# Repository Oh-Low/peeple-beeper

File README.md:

# PEEPLE BEEPER

A 128×64 FSTN LoRa pager. The C firmware under `firmware/` is shared by the desktop bench and the Feather nRF52840 image. The RP2350 board (v3, `hardware/rp2350`) has a schematic and no layout or firmware image yet. It replaces the ESP32-S3 board (v2).

Build, bench keys, and how to flash a Feather are below. The map of the tree is [docs/README.md](docs/README.md).

## Build

```
make test           # host tests, each prints ok
make bench          # build/peeple-emu (SDL2)
make run            # build it if needed, then open the window
make check-feather  # compile the Feather HAL table, no link and no flash
make bringup        # breadboard wire test, build/bringup.uf2
make flash-bringup  # copy that image onto FTHR840BOOT
make feather        # pager image, build/feather.uf2
make flash-feather  # copy that image onto FTHR840BOOT
```

`make feather` and `make bringup` need `arm-none-eabi-gcc`. Double-tap the Feather reset button so the `FTHR840BOOT` drive appears, then flash. The wire-test glass shows the switches, the compass ids, one radio register, and a count of GPS sentences. The pager image shows the menu.

`cmake -B build/cmake && cmake --build build/cmake` builds the same host tests and `peeple-emu`. It does not build a UF2.

## Bench

Install SDL2, then `make run`. On macOS, double-click `peeple-emu.command`.

```
brew install sdl2 pkg-config          # macOS
sudo apt install libsdl2-dev pkg-config   # Debian / Ubuntu
sudo dnf install SDL2-devel pkgconf-pkg-config   # Fedora
pacman -S mingw-w64-ucrt-x86_64-SDL2 mingw-w64-ucrt-x86_64-pkgconf   # MSYS2
```

Default bench is three radios at east 0 / 75 / 150 ft, all at north 0 (A reaches C only through B). **+ add** / **− remove** in the top bar grow the bench up to 16 units. Each column is a scaled 128×64 LCD, the radio name, its place on the foot grid, and who it can hear.

- Click an LCD to focus that radio
- Scroll or drag on the LCD = encoder
- Click = shaft press + release (Select)
- Esc = Back
- **N / W / E / S** move that radio on the foot grid. North is up. A step is 5 ft, Shift is 25 ft. Scrolling the panel under an LCD moves it north or south. Straight-line distance under 100 ft is radio range. `(1, 0)` is 1 ft east.
- **flat** / **tipped** and **still** / **moving** are the level check. Tipped is 25° off flat. **heading − / +** turns that radio. A step is 15°, Shift is 45°, and 0° means the top of the LCD points north.
- **sky** / **no sky** is whether a listen can see satellites. **sample** starts that listen now.
- j/k and arrows turn the knob; Enter/Space selects
- NVM is per user: `~/Library/Application Support/Peeple/Beeper/` on macOS, `~/.local/share/Peeple/Beeper/` on Linux, `%APPDATA%\Peeple\Beeper\` on Windows. A file still named `./emu-nvm-<id>.bin` in the current directory is read once, then saved in that folder.

The bench seeds contact books so A/B/C can Compose without walking HELLO. That directory is bench-only.

## Pair two pagers

1. Settings → Display name on each unit.
2. Add on both, hold the units together (RSSI ≥ −45).
3. Compose → peer name → canned line.

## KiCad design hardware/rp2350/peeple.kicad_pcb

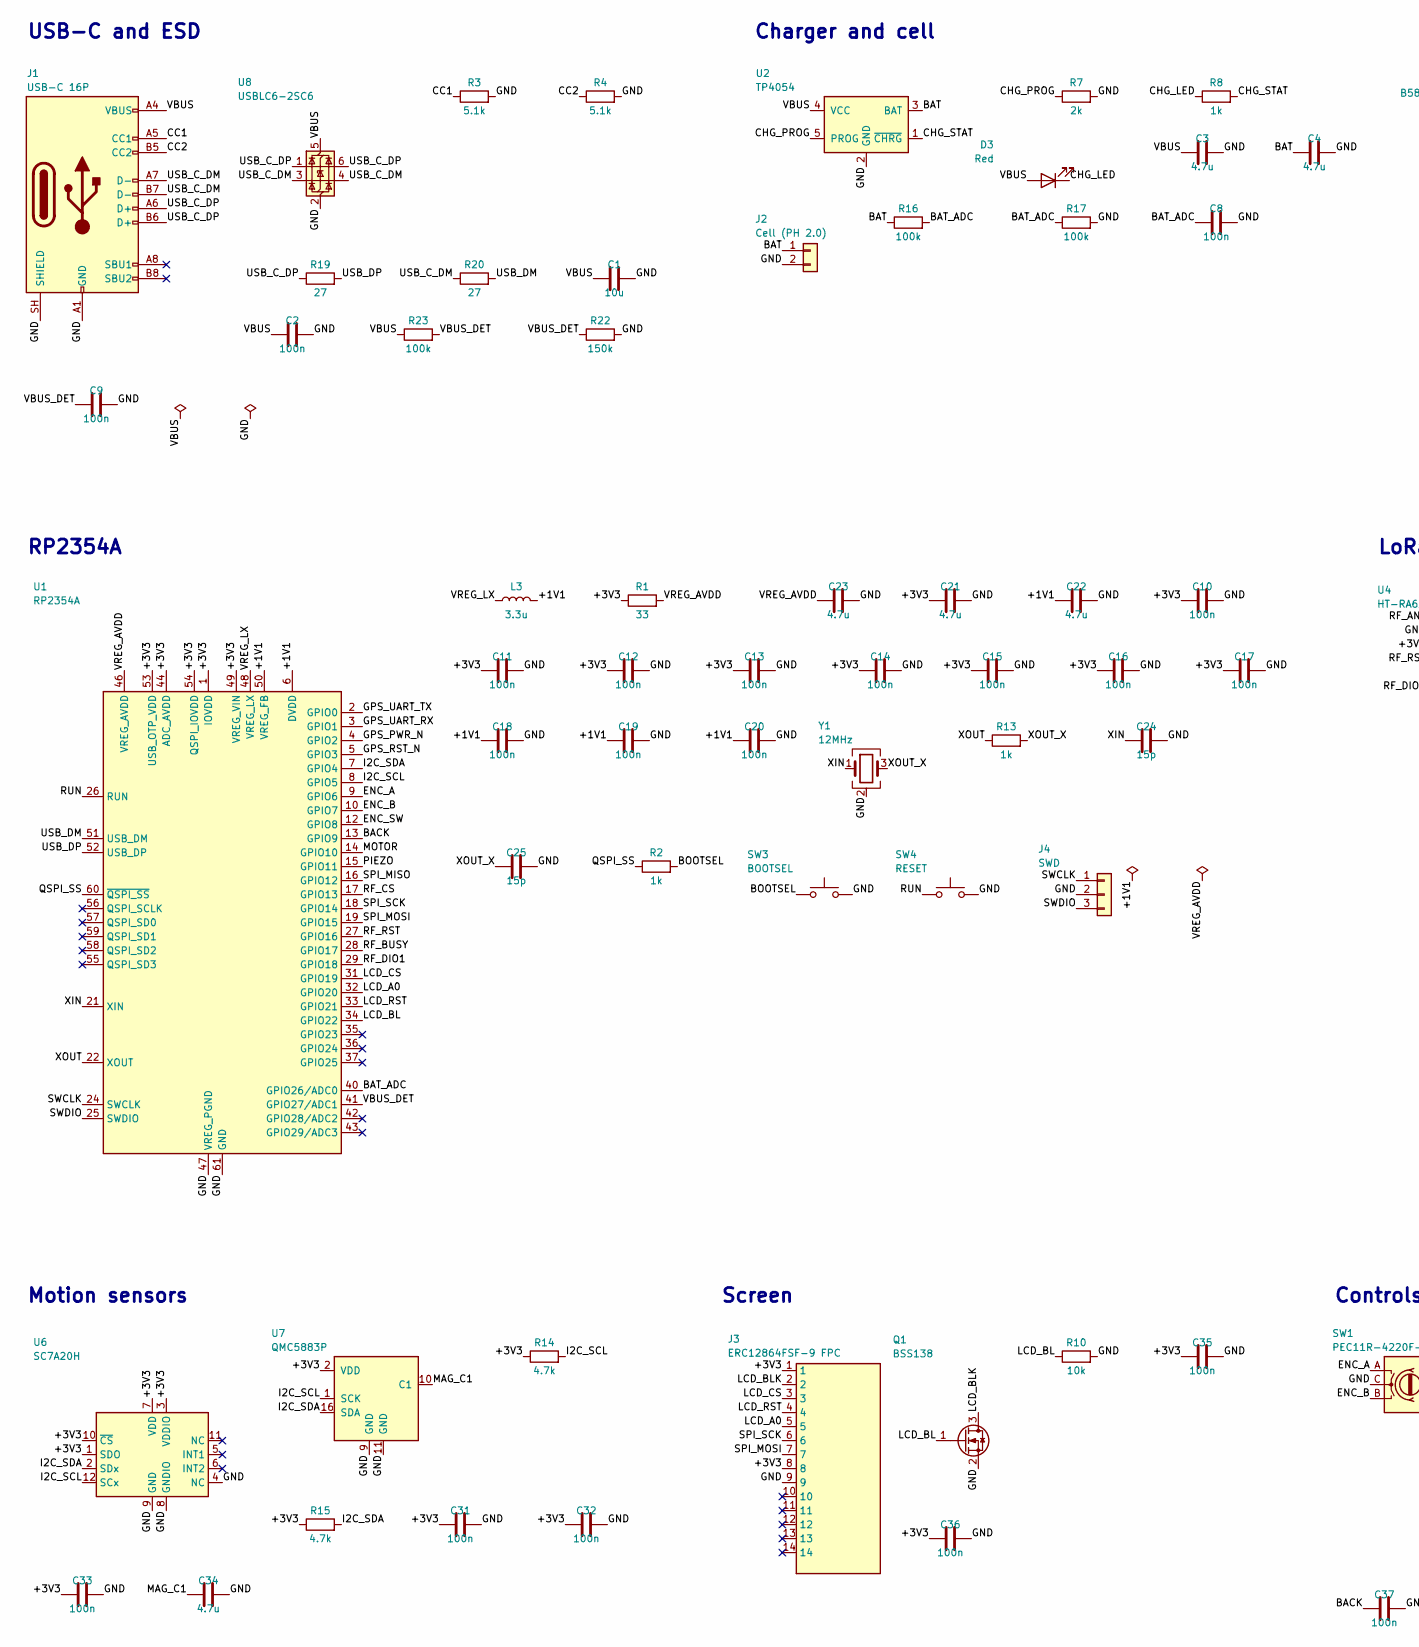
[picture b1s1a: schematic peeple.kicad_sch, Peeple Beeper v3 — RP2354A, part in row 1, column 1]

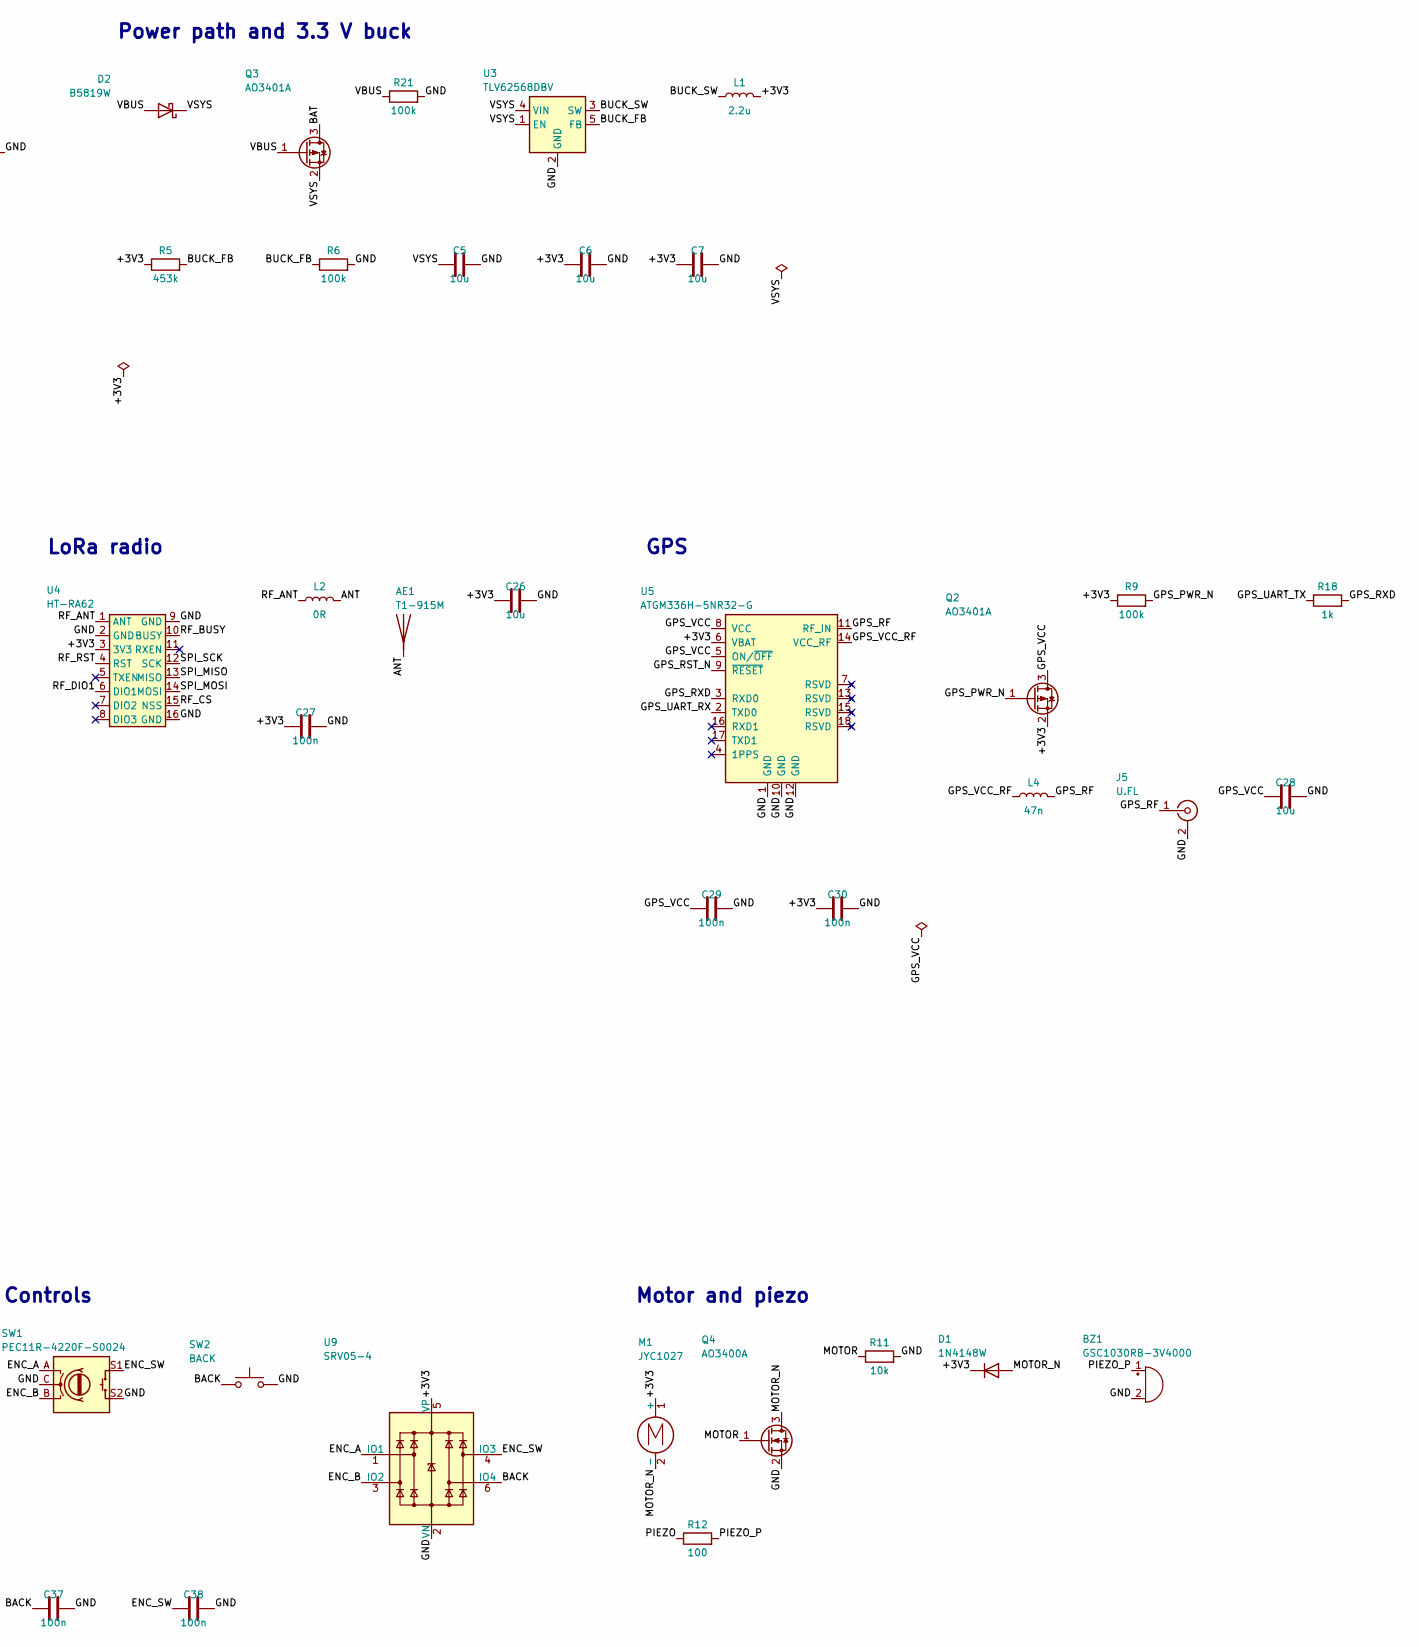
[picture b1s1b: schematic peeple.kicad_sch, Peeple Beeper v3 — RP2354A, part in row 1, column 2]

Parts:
AE1: T1-915M; MPN T1-915M; LCSC C726086
BZ1: GSC1030RB-3V4000; Piezo_10x10; MPN GSC1030RB-3V4000; LCSC C255330
C1, C5, C6, C7, C26, C28: 10u; C_0805_2012Metric_Pad1.18x1.45mm_HandSolder; MPN CL21A106KAYNNNE; LCSC C15850
C2, C8, C9, C27, C29, C30, C31, C32, C33, C35, C36, C37, C38: 100n; C_0805_2012Metric_Pad1.18x1.45mm_HandSolder; MPN CC0805KRX7R9BB104; LCSC C49678
C3, C4, C34: 4.7u; C_0805_2012Metric_Pad1.18x1.45mm_HandSolder; MPN CL21A475KAQNNNE; LCSC C1779
C10, C11, C12, C13, C14, C15, C16, C17, C18, C19, C20: 100n; C_0603_1608Metric_Pad1.08x0.95mm_HandSolder; MPN CC0603KRX7R9BB104; LCSC C14663
C21, C22, C23: 4.7u; C_0603_1608Metric_Pad1.08x0.95mm_HandSolder; MPN CL10A475KA8NQNC; LCSC C69335
C24, C25: 15p; C_0603_1608Metric_Pad1.08x0.95mm_HandSolder; MPN CL10C150JB8NNNC; LCSC C1644
D1: 1N4148W; D_SOD-123; MPN 1N4148W; LCSC C81598
D2: B5819W; D_SOD-123; MPN B5819W; LCSC C2943878
D3: Red; LED_0805_2012Metric_Pad1.15x1.40mm_HandSolder; MPN NCD0805R1; LCSC C84256
J1: USB-C 16P; USB_C_Receptacle_HRO_TYPE-C-31-M-12; MPN TYPE-C-31-M-12; LCSC C165948
J2: Cell (PH 2.0); JST_PH_S2B-PH-SM4-TB_1x02-1MP_P2.00mm_Horizontal; MPN PH-2PWB; LCSC C2905019
J3: ERC12864FSF-9 FPC; Molex_200528-0140_1x14-1MP_P1.00mm_Horizontal; MPN Molex 200528-0140
J4: SWD; PinHeader_1x03_P2.54mm_Vertical; MPN 2.54 mm 1x3 header (optional); LCSC C2337
J5: U.FL; U.FL_Hirose_U.FL-R-SMT-1_Vertical; MPN U.FL-R-SMT-1(80); LCSC C88374
L1: 2.2u; L_Sunlord_SWPA4030S; MPN FNR4030S2R2MT; LCSC C167869
L2: 0R; L_0805_2012Metric_Pad1.05x1.20mm_HandSolder; MPN 0805W8F0000T5E; LCSC C17477
L3: 3.3u; L_Abracon_AOTA-B201610S; MPN AOTA-B201610S3R3-101-T; LCSC C42411119
L4: 47n; L_0603_1608Metric_Pad1.05x0.95mm_HandSolder; MPN LQW18AN47NG00D; LCSC C98076
M1: JYC1027; Motor_Coin_10mm; MPN JYC1027
Q1: BSS138; SOT-23; MPN BSS138; LCSC C78284
Q2, Q3: AO3401A; SOT-23; MPN AO3401A; LCSC C15127
Q4: AO3400A; SOT-23; MPN AO3400A; LCSC C20917
R1: 33; R_0603_1608Metric_Pad0.98x0.95mm_HandSolder; MPN 0603WAF330JT5E; LCSC C23140
R2, R13: 1k; R_0603_1608Metric_Pad0.98x0.95mm_HandSolder; MPN 0603WAF1001T5E; LCSC C21190
R3, R4: 5.1k; R_0805_2012Metric_Pad1.20x1.40mm_HandSolder; MPN 0805W8F5101T5E; LCSC C27834
R5: 453k; R_0805_2012Metric_Pad1.20x1.40mm_HandSolder; MPN 0805W8F4533T5E; LCSC C17702
R6, R9, R16, R17, R21, R23: 100k; R_0805_2012Metric_Pad1.20x1.40mm_HandSolder; MPN 0805W8F1003T5E; LCSC C149504
R7: 2k; R_0805_2012Metric_Pad1.20x1.40mm_HandSolder; MPN 0805W8F2001T5E; LCSC C17604
R8, R18: 1k; R_0805_2012Metric_Pad1.20x1.40mm_HandSolder; MPN 0805W8F1001T5E; LCSC C17513
R10, R11: 10k; R_0805_2012Metric_Pad1.20x1.40mm_HandSolder; MPN 0805W8F1002T5E; LCSC C17414
R12: 100; R_0805_2012Metric_Pad1.20x1.40mm_HandSolder; MPN 0805W8F1000T5E; LCSC C17408
R14, R15: 4.7k; R_0805_2012Metric_Pad1.20x1.40mm_HandSolder; MPN 0805W8F4701T5E; LCSC C17673
R19, R20: 27; R_0603_1608Metric_Pad0.98x0.95mm_HandSolder; MPN 0603WAF270JT5E; LCSC C25190
R22: 150k; R_0805_2012Metric_Pad1.20x1.40mm_HandSolder; MPN 0805W8F1503T5E; LCSC C17470
SW1: PEC11R-4220F-S0024; RotaryEncoder_Alps_EC11E-Switch_Vertical_H20mm; MPN PEC11R-4220F-S0024
SW2: BACK; SW_Push_1P1T_XKB_TS-1187A; MPN TS-1187A-B-A-B; LCSC C318884
SW3: BOOTSEL; SW_Push_1P1T_XKB_TS-1187A; MPN TS-1187A-B-A-B; LCSC C318884
SW4: RESET; SW_Push_1P1T_XKB_TS-1187A; MPN TS-1187A-B-A-B; LCSC C318884
U1: RP2354A; QFN-60-1EP_7x7mm_P0.4mm_EP3.4x3.4mm; MPN RP2354A; LCSC C41378174
U2: TP4054; SOT-23-5; MPN TP4054; LCSC C668215
U3: TLV62568DBV; SOT-23-5; MPN TLV62568DBVR; LCSC C163219
U4: HT-RA62; MPN HT-RA62 (915 MHz)
U5: ATGM336H-5NR32-G; Quectel_L76; MPN ATGM336H-5NR32-G; LCSC C49233943
U6: SC7A20H; LGA-12_2x2mm_P0.5mm; MPN SC7A20HTR; LCSC C19274408
U7: QMC5883P; LGA-16_3x3mm_P0.5mm; MPN QMC5883P; LCSC C2847467
U8: USBLC6-2SC6; SOT-23-6; MPN USBLC6-2SC6; LCSC C2827654
U9: SRV05-4; SOT-23-6; MPN SRV05-4; LCSC C558418
Y1: 12MHz; Crystal_SMD_3225-4Pin_3.2x2.5mm_HandSoldering; MPN ABM8-272-T3; LCSC C20625731

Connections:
/+1V1: C18.1, C19.1, C20.1, C22.1, L3.2, U1.6 (DVDD), U1.23 (DVDD), U1.39 (DVDD), U1.50 (VREG_FB)
/+3V3: C6.1, C7.1, C10.1, C11.1, C12.1, C13.1, C14.1, C15.1, C16.1, C17.1, C21.1, C26.1, C27.1, C30.1, C31.1, C32.1, C33.1, C35.1, C36.1, D1.1 (K), J3.1, J3.8, L1.2, M1.1 (+), Q2.2 (S), R1.1, R5.1, R9.1, R14.1, R15.1, U1.1 (IOVDD), U1.11 (IOVDD), U1.20 (IOVDD), U1.30 (IOVDD), U1.38 (IOVDD), U1.44 (ADC_AVDD), U1.45 (IOVDD), U1.49 (VREG_VIN), U1.53 (USB_OTP_VDD), U1.54 (QSPI_IOVDD), U4.3 (3V3), U5.6 (VBAT), U6.1 (SDO), U6.3 (VDDIO), U6.7 (VDD), U6.10 (~CS), U7.2 (VDD), U9.5 (VP)
/ANT: AE1.1 (A_1), L2.2
/BACK: C37.1, SW2.1, U1.13 (GPIO9), U9.6 (IO4)
/BAT: C4.1, J2.1, Q3.3 (D), R16.1, U2.3 (BAT)
/BAT_ADC: C8.1, R16.2, R17.1, U1.40 (GPIO26/ADC0)
/BOOTSEL: R2.2, SW3.1
/BUCK_FB: R5.2, R6.1, U3.5 (FB)
/BUCK_SW: L1.1, U3.3 (SW)
/CC1: J1.A5 (CC1), R3.1
/CC2: J1.B5 (CC2), R4.1
/CHG_LED: D3.1 (K), R8.1
/CHG_PROG: R7.1, U2.5 (PROG)
/CHG_STAT: R8.2, U2.1 (~CHRG)
/ENC_A: SW1.A, U1.9 (GPIO6), U9.1 (IO1)
/ENC_B: SW1.B, U1.10 (GPIO7), U9.3 (IO2)
/ENC_SW: C38.1, SW1.S1, U1.12 (GPIO8), U9.4 (IO3)
/GND: BZ1.2 (-), C1.2, C2.2, C3.2, C4.2, C5.2, C6.2, C7.2, C8.2, C9.2, C10.2, C11.2, C12.2, C13.2, C14.2, C15.2, C16.2, C17.2, C18.2, C19.2, C20.2, C21.2, C22.2, C23.2, C24.2, C25.2, C26.2, C27.2, C28.2, C29.2, C30.2, C31.2, C32.2, C33.2, C34.2, C35.2, C36.2, C37.2, C38.2, J1.A1 (GND), J1.A12 (GND), J1.B1 (GND), J1.B12 (GND), J1.SH (SHIELD), J2.2, J3.9, J4.2, J5.2 (Ext), Q1.2 (S), Q4.2 (S), R3.2, R4.2, R6.2, R7.2, R10.2, R11.2, R17.2, R21.2, R22.2, SW1.C, SW1.S2, SW2.2, SW3.2, SW4.2, U1.47 (VREG_PGND), U1.61 (GND), U2.2 (GND), U3.2 (GND), U4.2 (GND), U4.9 (GND), U4.16 (GND), U5.1 (GND), U5.10 (GND), U5.12 (GND), U6.4 (NC), U6.8 (GNDIO), U6.9 (GND), U7.9 (GND), U7.11 (GND), U8.2 (GND), U9.2 (VN), Y1.2 (G), Y1.4 (G)
/GPS_PWR_N: Q2.1 (G), R9.2, U1.4 (GPIO2)
/GPS_RF: J5.1 (In), L4.2, U5.11 (RF_IN)
/GPS_RST_N: U1.5 (GPIO3), U5.9 (~RESET)
/GPS_RXD: R18.2, U5.3 (RXD0)
/GPS_UART_RX: U1.3 (GPIO1), U5.2 (TXD0)
/GPS_UART_TX: R18.1, U1.2 (GPIO0)
/GPS_VCC: C28.1, C29.1, Q2.3 (D), U5.5 (ON/~OFF), U5.8 (VCC)
/GPS_VCC_RF: L4.1, U5.14 (VCC_RF)
/I2C_SCL: R14.2, U1.8 (GPIO5), U6.12 (SCx), U7.1 (SCK)
/I2C_SDA: R15.2, U1.7 (GPIO4), U6.2 (SDx), U7.16 (SDA)
/LCD_A0: J3.5, U1.32 (GPIO20)
/LCD_BL: Q1.1 (G), R10.1, U1.34 (GPIO22)
/LCD_BLK: J3.2, Q1.3 (D)
/LCD_CS: J3.3, U1.31 (GPIO19)
/LCD_RST: J3.4, U1.33 (GPIO21)
/MAG_C1: C34.1, U7.10 (C1)
/MOTOR: Q4.1 (G), R11.1, U1.14 (GPIO10)
/MOTOR_N: D1.2 (A), M1.2 (-), Q4.3 (D)
/PIEZO: R12.1, U1.15 (GPIO11)
/PIEZO_P: BZ1.1 (+), R12.2
/QSPI_SS: R2.1, U1.60 (~QSPI_SS)
/RF_ANT: L2.1, U4.1 (ANT)
/RF_BUSY: U1.28 (GPIO17), U4.10 (BUSY)
/RF_CS: U1.17 (GPIO13), U4.15 (NSS)
/RF_DIO1: U1.29 (GPIO18), U4.6 (DIO1)
/RF_RST: U1.27 (GPIO16), U4.4 (RST)
/RUN: SW4.1, U1.26 (RUN)
/SPI_MISO: U1.16 (GPIO12), U4.13 (MISO)
/SPI_MOSI: J3.7, U1.19 (GPIO15), U4.14 (MOSI)
/SPI_SCK: J3.6, U1.18 (GPIO14), U4.12 (SCK)
/SWCLK: J4.1, U1.24 (SWCLK)
/SWDIO: J4.3, U1.25 (SWDIO)
/USB_C_DN: J1.A7 (D-), J1.B7 (D-), R20.1, U8.3 (I/O2), U8.4 (I/O2)
/USB_C_DP: J1.A6 (D+), J1.B6 (D+), R19.1, U8.1 (I/O1), U8.6 (I/O1)
/USB_DN: R20.2, U1.51 (USB_DM)
/USB_DP: R19.2, U1.52 (USB_DP)
/VBUS: C1.1, C2.1, C3.1, D2.2 (A), D3.2 (A), J1.A4 (VBUS), J1.A9 (VBUS), J1.B4 (VBUS), J1.B9 (VBUS), Q3.1 (G), R21.1, R23.1, U2.4 (VCC), U8.5 (VBUS)
/VBUS_DET: C9.1, R22.1, R23.2, U1.41 (GPIO27/ADC1)
/VREG_AVDD: C23.1, R1.2, U1.46 (VREG_AVDD)
/VREG_LX: L3.1, U1.48 (VREG_LX)
/VSYS: C5.1, D2.1 (K), Q3.2 (S), U3.1 (EN), U3.4 (VIN)
/XIN: C24.1, U1.21 (XIN), Y1.1
/XOUT: R13.1, U1.22 (XOUT)
/XOUT_X: C25.1, R13.2, Y1.3

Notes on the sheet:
USB-C and ESD
Charger and cell
Power path and 3.3 V buck
RP2354A
LoRa radio
GPS
Motion sensors
Screen
Controls
Motor and piezo

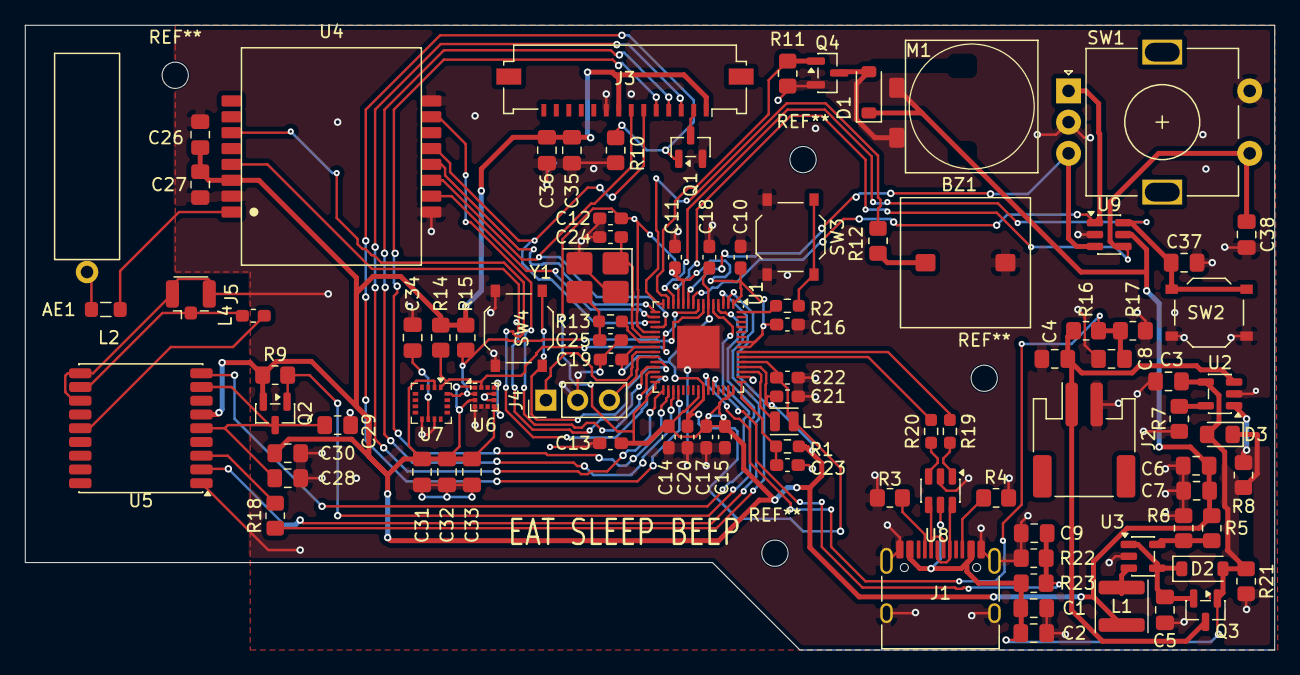
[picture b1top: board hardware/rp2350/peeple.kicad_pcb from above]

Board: 2 copper layers, 100.0 x 50.0 mm, 94 parts (0 on the bottom side), 62 nets.

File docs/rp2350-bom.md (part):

# RP2350 bill of materials

Parts for the v3 board, ten units, built by hand with a hotplate and an iron. Prices are the LCSC, DigiKey, Heltec, and BuyDisplay product pages on 25 November 2026, at the price break the ten-board order reaches, rounded to the cent. Shipping, tariffs, the stencil, and the bare boards are not in the total.

Reference designators match [RP2350 connections](rp2350-connections.md) and `hardware/rp2350/peeple.kicad_sch`. The v2 ESP32 list is [esp32-bom.md](esp32-bom.md). There is no RP2350 firmware image in this tree yet; what the port needs is in [rp2350-bringup.md](rp2350-bringup.md).

One cell. USB and the cell share `VSYS` (Schottky D2 from USB, P-FET Q3 from the cell). One TLV62568 makes `+3V3` from `VSYS`. That rail feeds the RP2354A, radio, screen, GPS (switched), sensors, backlight, motor, and piezo. The RP2354A makes its own 1.1 V core rail with L3.

## Quoted parts

One of each ref per board unless the Ref column lists more. New spec PDFs are in [`rp2350-datasheets/`](rp2350-datasheets/). Parts carried over from v2 link to [`esp32-datasheets/`](esp32-datasheets/).

| Ref | Role | Part | Order number | Vendor | Spec | Each | Ten |
|---|---|---|---|---|---|---:|---:|
| U1 | MCU, 2 MB flash inside | Raspberry Pi RP2354A | C41378174 | LCSC | [PDF](https://datasheets.raspberrypi.com/rp2350/rp2350-datasheet.pdf) | $1.24 | $12.38 |
| Y1 | 12 MHz crystal | Abracon ABM8-272-T3 | C20625731 | LCSC | [guide](https://datasheets.raspberrypi.com/rp2350/hardware-design-wi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 | $0.40 | $4.00 |
| L3 | Core regulator inductor, 3.3 µH | Abracon AOTA-B201610S3R3-101-T | C42411119 | LCSC | [guide](https://datasheets.raspberrypi.com/rp2350/hardware-design-wi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 | $0.32 | $3.16 |
| J1 | USB-C jack, 16 pin | HRO TYPE-C-31-M-12 | C165948 | LCSC | [PDF](rp2350-datasheets/TYPE-C-31-M-12.pdf) | $0.17 | $1.74 |
| U8 | USB ESD | USBLC6-2SC6 | C2827654 | LCSC | [PDF](rp2350-datasheets/USBLC6-2SC6.pdf) | $0.05 | $0.45 |
| U2 | Li-ion charger | TPOWER TP4054 | C668215 | LCSC | [PDF](rp2350-datasheets/TP4054.pdf) | $0.04 | $0.39 |
| U3 | 3.3 V buck | TI TLV62568DBVR | C163219 | LCSC | [PDF](esp32-datasheets/TLV62568.pdf) | $0.08 | $0.76 |
| L1 | Buck inductor, 2.2 µH | Changjiang FNR4030S2R2MT | C167869 | LCSC | — | $0.08 | $0.79 |
| D2 | USB to VSYS Schottky | B5819W, SOD-123 | C2943878 | LCSC | — | $0.02 | $0.15 |
| Q2, Q3 | GPS switch, cell to VSYS | AOS AO3401A | C15127 | LCSC | [PDF](https://www.aosmd.com/sites/default/files/res/datasheets/AO3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 | $0.17 | $1.65 |
| U4 | Radio, 902–928 MHz | Heltec HT-RA62 | ZC-144-915 | [Heltec](https://heltec.org/project/ht-ra62/) | [PDF](esp32-datasheets/HT-RA62.pdf) | $3.90 | $39.00 |
| AE1 | 915 MHz antenna | DreamLNK T1-915M | C726086 | LCSC | [PDF](esp32-datasheets/DreamLNK-T1-915M.pdf) | $0.24 | $2.39 |
| U5 | GPS module | Zhongke ATGM336H-5NR32-G | C49233943 | LCSC | [PDF](rp2350-datasheets/ATGM336H-5NR32-G.pdf) | $1.68 | $16.75 |
| — | GPS active patch on IPEX cable | Bat Wireless BWGPSCNX8-8B1 | C496567 | LCSC | — | $1.59 | $15.90 |
| J5 | GPS antenna jack | Hirose U.FL-R-SMT-1(80) | C88374 | LCSC | — | $0.10 | $1.04 |
| L4 | GPS antenna bias, 47 nH | Murata LQW18AN47NG00D | C98076 | LCSC | — | $0.05 | $0.52 |
| U6 | Accelerometer | Silan SC7A20HTR | C19274408 | LCSC | [PDF](rp2350-datasheets/SC7A20H.pdf) | $0.22 | $2.16 |
| U7 | Magnetometer | QST QMC5883P | C2847467 | LCSC | [PDF](rp2350-datasheets/QMC5883P.pdf) | $1.86 | $18.60 |
| — | Screen glass, 1.7 inch FPC | EastRising ERC12864FSF-9 | ERC12864FSF-9 | BuyDisplay | [PDF](esp32-datasheets/ERC12864-9_Datasheet.pdf) | $2.12 | $21.20 |
| J3 | Screen socket | Molex 200528-0140 | — | BuyDisplay | [PDF](esp32-datasheets/Molex_200528.pdf) | $0.16 | $1.60 |
| Q1 | Backlight switch | BSS138 | C78284 | LCSC | — | $0.02 | $0.21 |
| SW1 | Encoder with push | Bourns PEC11R-4220F-S0024 | C143797 | LCSC | [PDF](esp32-datasheets/PEC11R.pdf) | $2.33 | $23.30 |
| SW2–SW4 | Back, BOOTSEL, RESET | XKB TS-1187A-B-A-B | C318884 | LCSC | — | $0.06 | $0.59 |
| U9 | Encoder and button ESD | SRV05-4 | C558418 | LCSC | [PDF](rp2350-datasheets/SRV05-4.pdf) | $0.03 | $0.26 |
| M1 | Coin motor | Jie Yi JYC1027 | JYC1027 | DigiKey | — | $1.24 | $12.36 |
| Q4 | Motor switch | AOS AO3400A | C20917 | LCSC | [PDF](https://www.aosmd.com/sites/default/files/res/datasheets/AO3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 | $0.08 | $0.79 |
| D1 | Motor flyback | 1N4148W, SOD-123 | C81598 | LCSC | — | $0.01 | $0.12 |
| BZ1 | Piezo, 4 kHz | INGHAi GSC1030RB-3V4000 | C255330 | LCSC | [PDF](esp32-datasheets/GSC1030RB-3V4000.pdf) | $0.49 | $4.86 |
| J2 | Cell header, PH 2.0 | DEALON PH-2PWB | C2905019 | LCSC | [PDF](rp2350-datasheets/PH-2PWB.pdf) | $0.03 | $0.32 |
| D3 | Charge LED, red 0805 | NCD0805R1 | C84256 | LCSC | — | $0.01 | $0.12 |
| J4 | SWD header, optional | 1×40 2.54 mm strip, cut to 3 | C2337 | LCSC | — | $0.02 | $0.16 |
| — | Cell, 2000 mAh | Adafruit 2011, 60 × 36 × 7 mm | 2011 | DigiKey | [page](https://www.digikey.com/en/products/detail/adafruit-industri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 | $12.50 | $125.00 |
| — | Passives | Listed in the next section | — | LCSC | — | $0.69 | $6.92 |
| | **Parts** | | | | | **$31.96** | **$319.64** |

Each and Ten are what the parts that go on the boards cost at the BOM vendor (cell line still shows DigiKey Adafruit for a known-good quote). The live shopping cart uses the AliExpress 103450 pouch at $1.80: [rp2350-shopping-list.md](rp2350-shopping-list.md) is **$224.74** cart ($22.47 / board), or **$208.79** allocated ($20.88 / board) if leftovers are ignored.

v2 was $38.76 a board with the $7.25 LaskaKit cell. That cell is out of stock, and v3 uses the $12.50 Adafruit cell instead. With the same cell, v3 would be $26.71, $12.05 less than v2. Most of it is the GPS ($7.53 module → $3.42 with antenna, jack, and choke), the MCU ($4.78 module → about $2.17 with crystal, inductor, and its passives), and the cheaper connectors, charger, ESD, and power path.

The SWD header line is one 40-pin strip; it covers 13 boards.

There is no v3 layout yet. A board drawn from this schematic will need a stencil for U1 (QFN-60, 0.4 mm pitch), U6 (LGA-12), and U7 (LGA-16).

## Passives

Inside the $0.69 line. Refs and values match [RP2350 connections](rp2350-connections.md). 0805 hand-solder footprints everywhere except the parts that crowd U1, which are 0603.

| Qty | Ref | Value | Size | Order number | Role |
|---:|---|---|---|---|---|
| 2 | R3, R4 | 5.1 kΩ | 0805 | C27834 | USB-C CC1 and CC2 to ground |
| 2 | R19, R20 | 27 Ω | 0603 | C25190 | USB D+ and D− series, next to U1 |
| 1 | R23 | 100 kΩ | 0805 | C149504 | VBUS detect top |
| 1 | R22 | 150 kΩ | 0805 | C17470 | VBUS detect bottom (~3.0 V on GPIO27 at 5 V) |
| 1 | C9 | 100 nF | 0805 | C49678 | Across `VBUS_DET` |
| 2 | C1, C2 | 10 µF, 100 nF | 0805 | C15850, C49678 | VBUS at the jack |
| 1 | R7 | 2 kΩ | 0805 | C17604 | Charger PROG → 500 mA |
| 1 | R8 | 1 kΩ | 0805 | C17513 | Charge LED |
| 2 | C3, C4 | 4.7 µF | 0805 | C1779 | Charger VBUS and BAT |
| 2 | R16, R17 | 100 kΩ | 0805 | C149504 | Cell divider onto GPIO26 |
| 1 | C8 | 100 nF | 0805 | C49678 | Across `BAT_ADC` |
| 1 | R21 | 100 kΩ | 0805 | C149504 | Q3 gate to ground when USB is absent |
| 2 | R5, R6 | 453 kΩ, 100 kΩ | 0805 | C17702, C149504 | Buck feedback → 3.32 V |
| 3 | C5, C6, C7 | 10 µF | 0805 | C15850 | Buck input (`VSYS`) and output (`+3V3`) |
| 1 | R1 | 33 Ω | 0603 | C23140 | VREG_AVDD filter |
| 3 | C21, C22, C23 | 4.7 µF | 0603 | C69335 | VREG_VIN, `+1V1` output, VREG_AVDD |
| 11 | C10–C20 | 100 nF | 0603 | C14663 | One per U1 supply pin (53 and 54 share C16) |
| 1 | R13 | 1 kΩ | 0603 | C21190 | Crystal drive limit on XOUT |
| 2 | C24, C25 | 15 pF | 0603 | C1644 | Crystal load |
| 1 | R2 | 1 kΩ | 0603 | C21190 | BOOTSEL button into QSPI_SS |
| 1 | L2 | 0 Ω | 0805 | C17477 | Antenna link |
| 2 | C26, C27 | 10 µF, 100 nF | 0805 | C15850, C49678 | Radio supply |
| 1 | R9 | 100 kΩ | 0805 | C149504 | `GPS_PWR_N` pull-up (GPS off at reset) |
| 1 | R18 | 1 kΩ | 0805 | C17513 | GPS RXD series |
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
